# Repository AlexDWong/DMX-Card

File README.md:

# DMX-Card

## Description
The DMX-Card is a small breakout board that allows developers to quickly add a UART-to-DMX (RS-485) circuit to their designs. It has been designed to cut down on the time spent constructing isolated DMX-512 circuits for prototype designs. The circuit is fully isolated and protected against ESD, and can be easily configured with a 3-pin XLR, 5-pin XLR, or 0.100" connector of the user's choice.

## Updates
**9/24/2016:** Board version 1.1; see directory for changes

**9/22/2016:** Board version 1.0 proven

## Features
* +5V input with polarity and over-current protection
* Full power and data isolation
  * Isolated DC-DC converter (1.5kVDC)
  * Isolated I/O via optocoupler (2.5kVDC)
  * ESD protection on all data inputs and outputs (including DMX)
* Full DMX compliance*
  * ANSI E1.20-2006 RDM compliant circuit, including correct biasing resistors (562/133/562)
  * 10MBd optocouplers
* User-selectable connectors:
  * Output: 
    * Neutrik NC3FAH (3-pin XLR)
    * Neutrik NC5FAH (5-pin XLR)
    * 0.100" PTH connectors (headers, screw terminal blocks, etc.)
  * Input:
    * 0.100" PTH connectors (headers, screw terminal blocks, etc.)

## Physical
* Board Dimensions: 0.95" x 1.90" (24.13mm x 48.26mm) (Actual dimensions will vary depending on the type of output connector installed)
* Board Thickness: 1.6mm
* Input Power: +5VDC, 60mA (nominal)
* Input Connections: +5V, GND, RX, TX, RX/TX Select
* Output: Isolated RS-485/DMX-512 (GND-ISO, D-, D+)
* Mounting: 4x 0.125" holes, located at edges of board

**circuit is constructed to ANSI E1.20; RDM must be correctly implemented on controller for full compliance*

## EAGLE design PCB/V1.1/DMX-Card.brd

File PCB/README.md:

# PCB Files

This director contains all the files needed to modify the design of the DMX-Card. Revisions are separated into sub-directories, each of which contain the following files:

* Eagle `.BRD` and `.SCH` files (generated in Eagle 7.6.0)
* Board and schematic `.PNG` files for ease-of-access
* Gerber files
* Bill of Materials

Please note the following:
* All Eagle files have been checked for ERC and DRC errors using rule files provided by Elecrow. **If you choose to use a different fab house, please ensure that the boards meet their DRC requirements.**
* Similarly, the Gerber files have been generated using a CAM file provided by Elecrow; if you are planning to utilize a different fab house, you should either check to ensure they can accept the Gerber files located in this repository or generate your own Gerber files from the Eagle board and schematic files.

## Versions
### Version 1.1
Resolved several issues with version 1.0:
* Mounting holes in V1.0 were placed close to the edge of the board, which resulted in a high probability of edge breakage when depanelizing the boards. As a result, mounting holes have been reworked for greater clearance; note that some holes may be inaccessible depending on the connector choice.
* Input header moved away from the edge of the board to improve screw terminal block support.
* Electrolytic capacitor footprint removed; it was initially included in case additional decoupling was needed, but after testing the existing decoupling is satisfactory.
* Improved SMD component placement for easier hand-soldering. Namely, the two 10uF decoupling capacitors on the isolated side have been spaced further apart from each other, and the SM712 diode has been moved away from R9.
* Improved silkscreen layout to avoid conflicts with pads and vias.

### Version 1.0
Initial release. This version has been tested and is proven to work as described.

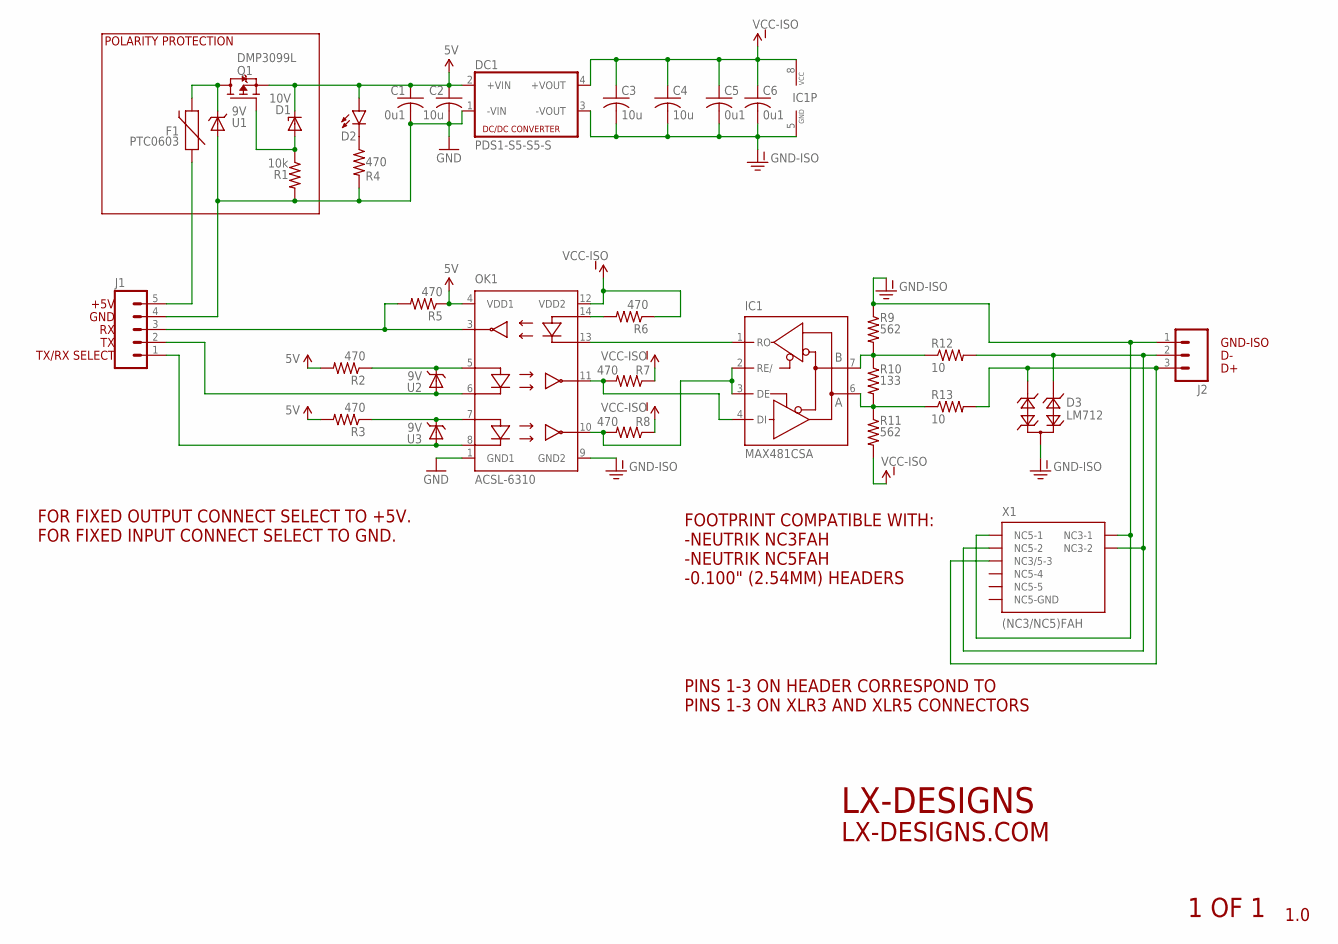
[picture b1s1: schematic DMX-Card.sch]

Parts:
C1, C5, C6: 0u1; C0603K
C2, C3, C4: 10u; C0603K
D1: 10V; SOD323
D2: LED0603; LED-0603
D3: LM712; SOT23
DC1: PDS1-S5-S5-S; 4SIL
F1: PTC0603; 0603
IC1: MAX481CSA; SO08
J1: M05NO_SILK; 1X05_NO_SILK
J2: M031X03_NO_SILK; 1X03_NO_SILK
OK1: ACSL-6310; SO-16
Q1: DMP3099L; SOT23
R1: 10k; R0603
R2, R3, R4, R5, R6, R7, R8: 470; R0603
R9, R11: 562; R0603
R10: 133; R0603
R12, R13: 10; R0603
U1, U2, U3: 9V; SOD323-NOSILK
X1: (NC3/NC5)FAH; NC3FAH-NC5FAH-NOSILK

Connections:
5V: C1.1, C2.1, D1.C, D2.A, DC1.2 (+VIN), OK1.4 (VDD1), Q1.2 (S), R2.2, R3.2, R5.1
D+: D3.2, J2.3, R13.2, X1.NC3-3 (NC3/5-3)
D-: D3.1, J2.2, R12.2, X1.NC3-2, X1.NC5-2
GND: C1.2, C2.2, DC1.1 (-VIN), J1.4, OK1.1 (GND1), R1.2, R4.2, U1.A
GND-ISO: C3.2, C4.2, C5.2, C6.2, D3.3, DC1.3 (-VOUT), IC1.5 (GND), J2.1, OK1.9 (GND2), R9.1, X1.NC3-1, X1.NC5-1
unnamed: IC1.7 (B), R9.2, R10.1, R12.1
unnamed: IC1.6 (A), R10.2, R11.1, R13.1
unnamed: F1.1, J1.5
unnamed: D2.C, R4.1
unnamed: IC1.1 (RO), OK1.13 (C3)
unnamed: OK1.5 (A1), R2.1, U2.C
unnamed: OK1.14 (A3), R6.2
unnamed: J1.3, OK1.3 (V03), R5.2
unnamed: IC1.4 (DI), OK1.11 (VO1), R7.2
unnamed: OK1.7 (A2), R3.1, U3.C
unnamed: J1.2, OK1.6 (C1), U2.A
unnamed: F1.2, Q1.3 (D), U1.C
unnamed: J1.1, OK1.8 (C2), U3.A
unnamed: D1.A, Q1.1 (G), R1.1
OPTO-OUT: IC1.2 (RE/), IC1.3 (DE), OK1.10 (VO2), R8.2
VCC-ISO: C3.1, C4.1, C5.1, C6.1, DC1.4 (+VOUT), IC1.8 (VCC), OK1.12 (VDD2), R6.1, R7.1, R8.1, R11.2

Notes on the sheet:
+5V
GND
TX/RX SELECT
PINS 1-3 ON HEADER CORRESPOND TO PINS 1-3 ON XLR3 AND XLR5 CONNECTORS
GND-ISO
FOR FIXED OUTPUT CONNECT SELECT TO +5V. FOR FIXED INPUT CONNECT SELECT TO GND.
1.0
LX-DESIGNS
POLARITY PROTECTION
FOOTPRINT COMPATIBLE WITH: -NEUTRIK NC3FAH -NEUTRIK NC5FAH -0.100" (2.54MM) HEADERS
LX-DESIGNS.COM
1 OF 1

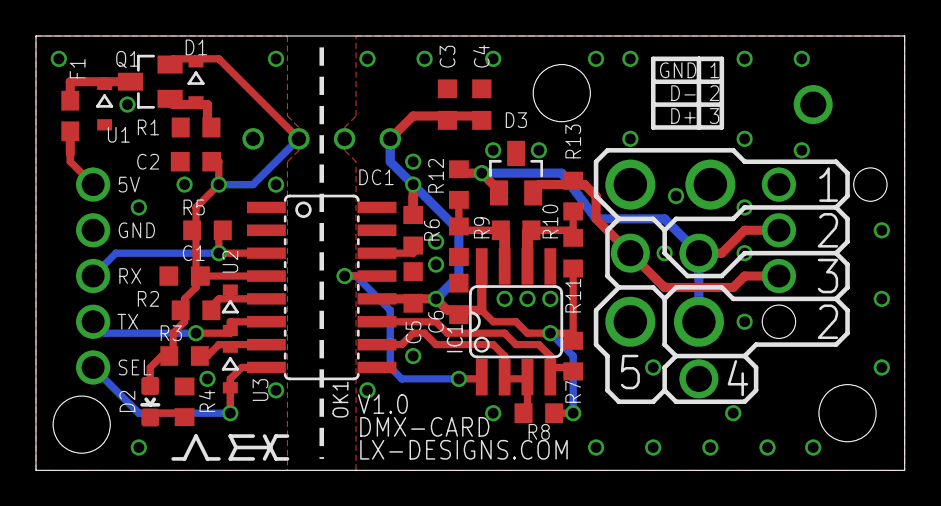
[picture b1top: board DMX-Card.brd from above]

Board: 2 copper layers, 48.3 x 24.1 mm, 33 parts (0 on the bottom side), 21 nets.

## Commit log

2016-09-13 [UNPROVEN] PCB version 1.0
2016-09-13 update gerbers
2016-09-17 Update BOM
2016-09-22 PCB images
2016-09-24 Revision 1.1
2016-09-24 V1.1 changelog
2016-09-29 License

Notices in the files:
parts and their libraries:
SparkFun-Aesthetics: Licensing: Creative Commons ShareAlike 4.0 International - https://creativecommons.org/licenses/by-sa/4.0
